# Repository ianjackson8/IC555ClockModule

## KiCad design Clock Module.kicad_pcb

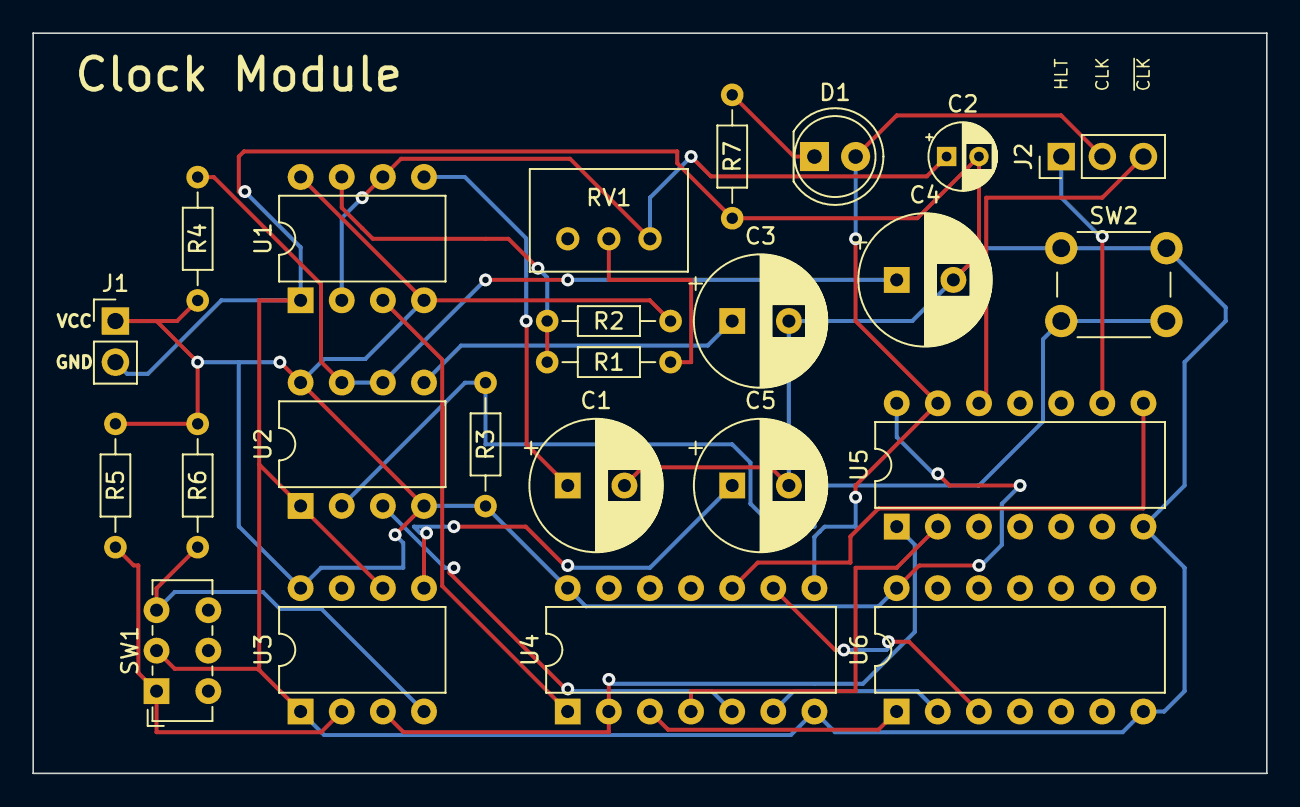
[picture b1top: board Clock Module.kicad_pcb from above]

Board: 2 copper layers, 76.2 x 45.7 mm, 24 parts (0 on the bottom side), 24 nets.

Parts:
C1, C3, C4, C5: 0.01µF; CP_Radial_D8.0mm_P3.50mm
C2: 1µF; CP_Radial_D4.0mm_P2.00mm
D1: LED; LED_D5.0mm
J1: Conn_01x02_Female; PinHeader_1x02_P2.54mm_Vertical
J2: Conn_01x03_Female; PinHeader_1x03_P2.54mm_Vertical
R1, R2, R3, R5, R6: 1k; R_Axial_DIN0204_L3.6mm_D1.6mm_P7.62mm_Horizontal
R4: 1M; R_Axial_DIN0204_L3.6mm_D1.6mm_P7.62mm_Horizontal
R7: 220; R_Axial_DIN0204_L3.6mm_D1.6mm_P7.62mm_Horizontal
RV1: R_Potentiometer; Potentiometer_Bourns_3299W_Vertical
SW1: SW_DPDT_x2; SW_E-Switch_EG1271_DPDT
SW2: SW_Push; SW_PUSH_6mm_H7.3mm
U1, U2, U3: LM555xN; DIP-8_W7.62mm
U4: 74LS08; DIP-14_W7.62mm
U5: 74LS04; DIP-14_W7.62mm
U6: 74LS32; DIP-14_W7.62mm

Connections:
/CLK: D1.2 (A), J2.2, U4.8, U5.13
/HLT: J2.1, U5.9
/~CLK: J2.3, U5.12
GNDREF: C1.2, C2.2, C3.2, C4.2, C5.2, J1.2, R7.2, SW1.2 (B), SW2.1, U1.1 (GND), U2.1 (GND), U3.1 (GND), U3.6 (THR), U4.7 (GND), U5.7 (GND), U6.7 (GND)
unnamed: C1.1, U1.5 (CV)
unnamed: C2.1, RV1.3, U1.2 (TR), U1.6 (THR)
unnamed: C3.1, U2.5 (CV)
unnamed: C4.1, R4.2, U2.6 (THR), U2.7 (DIS)
unnamed: C5.1, U3.5 (CV)
unnamed: D1.1 (K), R7.1
unnamed: R1.2, R2.1, U1.7 (DIS)
unnamed: R2.2, RV1.2
unnamed: R3.2, SW2.2, U2.2 (TR)
unnamed: R5.2, SW1.1 (A), U3.2 (TR)
unnamed: R6.2, SW1.3 (C), U3.4 (R)
unnamed: U1.3 (Q), U4.1
unnamed: U2.3 (Q), U4.5
unnamed: U3.3 (Q), U4.2, U5.1
unnamed: U4.3, U6.1
unnamed: U4.4, U5.2
unnamed: U4.6, U6.2
unnamed: U4.9, U6.3
unnamed: U4.10, U5.8
VCC: J1.1, R1.1, R3.1, R4.1, R5.1, R6.1, U1.4 (R), U1.8 (VCC), U2.4 (R), U2.8 (VCC), U3.8 (VCC), U4.14 (VCC), U5.14 (VCC), U6.14 (VCC)
